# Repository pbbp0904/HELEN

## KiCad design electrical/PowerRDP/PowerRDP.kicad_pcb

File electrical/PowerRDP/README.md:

# RDP-Power
This is a PCB designed in KiCad for the UAH SHC HELEN project's Radiation Detection Payload (RDP).  This PCB is intended to receive power from 2-3 18650 battery "banks" with 2 batteries connecting to each of J1:6.  Then the voltage is stepped to appropriate levels for the power requirements of the RDP payload (+/-15V, +12V and +3.3V).  A BOM will be attached after a parts list is fully compiled.

The rendering above is a rough idea of what this payload will look like with most of its components installed.  It is only missing the +/-15 V regulator in the bottom right and the mounting screws.

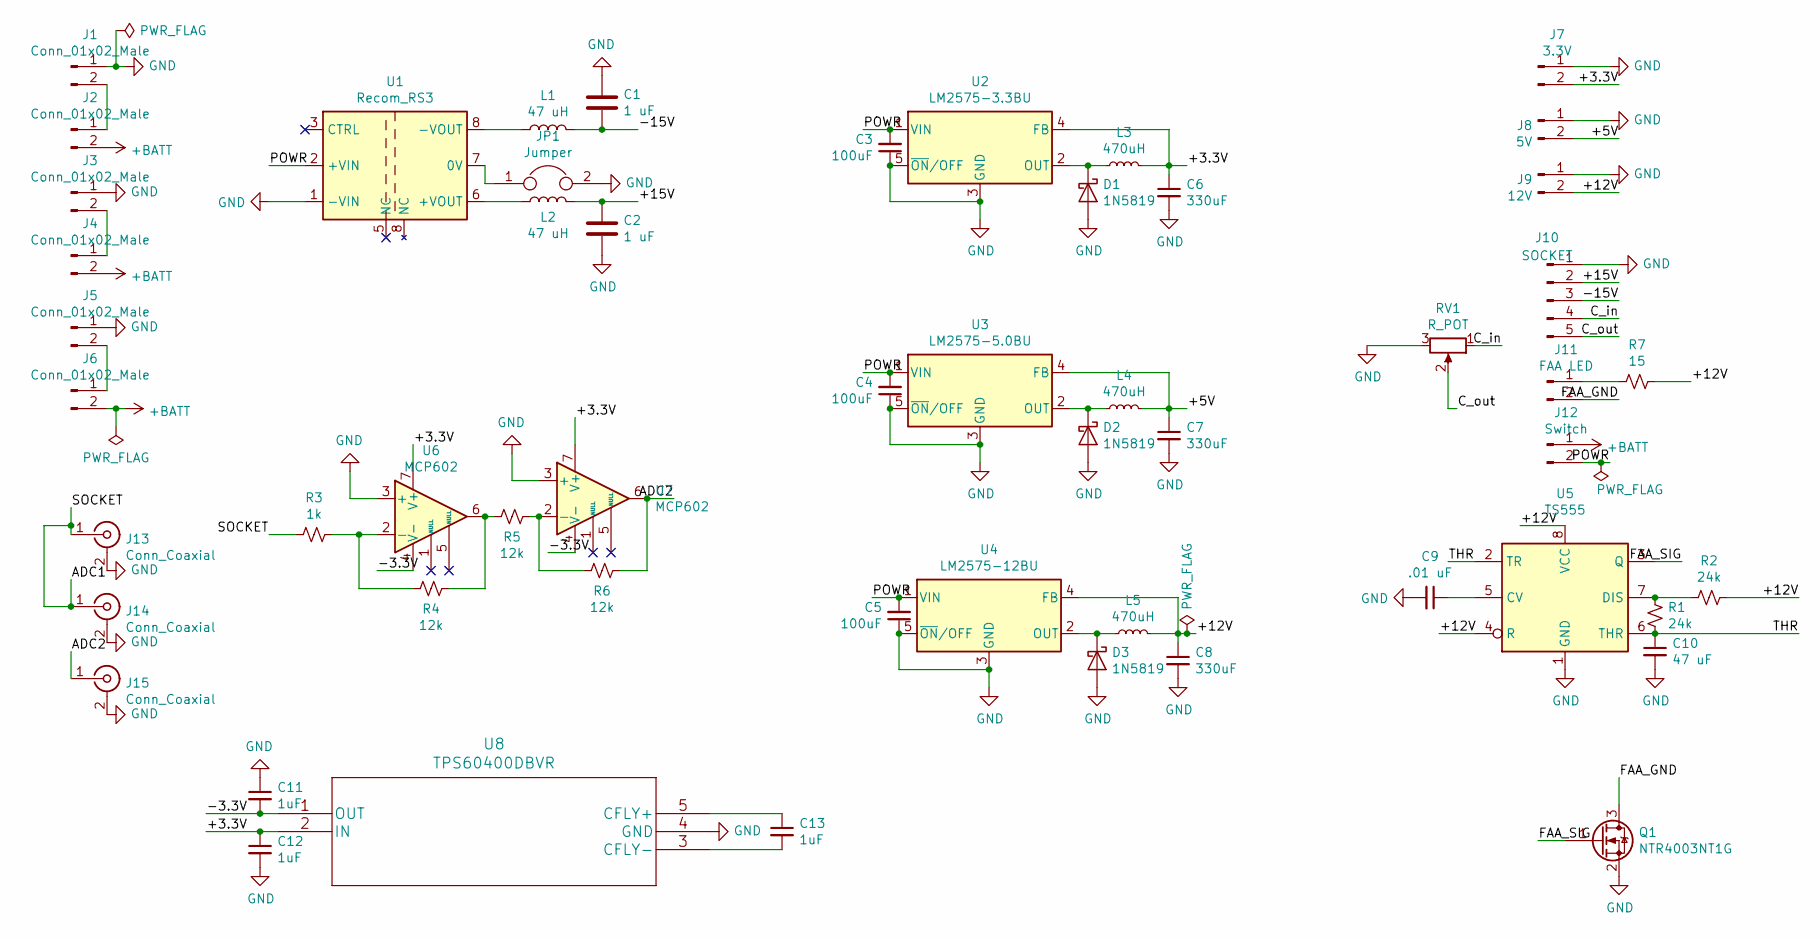
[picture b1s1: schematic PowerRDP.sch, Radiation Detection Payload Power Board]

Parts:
C1, C2: 1 uF; C_0805_2012Metric_Pad1.15x1.40mm_HandSolder
C3, C4, C5: 100uF; CP_Elec_6.3x7.7
C6, C7, C8: 330uF; CP_Elec_8x10
C9: .01 uF; C_0805_2012Metric_Pad1.15x1.40mm_HandSolder
C10: 47 uF; C_0805_2012Metric_Pad1.15x1.40mm_HandSolder
C11, C12, C13: 1uF; C_0805_2012Metric_Pad1.15x1.40mm_HandSolder
D1, D2, D3: 1N5819; D_SOD-123
J1, J2, J3, J4, J5, J6: Conn_01x02_Male; Molex_KK-254_AE-6410-02A_1x02_P2.54mm_Vertical
J7: 3.3V; Molex_KK-254_AE-6410-02A_1x02_P2.54mm_Vertical
J8: 5V; Molex_KK-254_AE-6410-02A_1x02_P2.54mm_Vertical
J9: 12V; Molex_KK-254_AE-6410-02A_1x02_P2.54mm_Vertical
J10: SOCKET; Molex_KK-254_AE-6410-05A_1x05_P2.54mm_Vertical
J11: FAA LED; Molex_KK-254_AE-6410-02A_1x02_P2.54mm_Vertical
J12: Switch; Molex_KK-254_AE-6410-02A_1x02_P2.54mm_Vertical
J13, J14, J15: Conn_Coaxial; SMA_Amphenol_132134_Vertical
JP1: Jumper; SolderJumper-2_P1.3mm_Open_Pad1.0x1.5mm
L1, L2: 47 uH; Murata 8200
L3, L4, L5: 470uH; L_Bourns_SRR1260
Q1: NTR4003NT1G; TSOT-23_HandSoldering
R1, R2: 24k; R_0805_2012Metric_Pad1.15x1.40mm_HandSolder
R3: 1k; R_Axial_DIN0204_L3.6mm_D1.6mm_P5.08mm_Horizontal
R4, R5, R6: 12k; R_0805_2012Metric_Pad1.15x1.40mm_HandSolder
R7: 15; R_0805_2012Metric_Pad1.15x1.40mm_HandSolder
RV1: R_POT; Potentiometer_Bourns_3214W_Vertical
U1: Recom_RS3
U2: LM2575-3.3BU; TO-263-5_TabPin3
U3: LM2575-5.0BU; TO-263-5_TabPin3
U4: LM2575-12BU; TO-263-5_TabPin3
U5: TS555; SOIC-8_3.9x4.9mm_P1.27mm
U6, U7: MCP602; SOIC-8_3.9x4.9mm_P1.27mm
U8: TPS60400DBVR

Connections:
+BATT: J2.2, J4.2, J6.2, J12.1
/+3.3V: C6.1, C12.1, J7.2, L3.2, U2.4 (FB), U6.7 (V+), U7.7 (V+), U8.2 (IN)
/+5V: C7.1, J8.2, L4.2, U3.4 (FB)
/+12V: C8.1, J9.2, L5.2, R2.1, R7.1, U4.4 (FB), U5.4 (R), U5.8 (VCC)
/+15V: C2.1, J10.2, L2.2
/-3.3V: C11.2, U6.4 (V-), U7.4 (V-), U8.1 (OUT)
/-15V: C1.1, J10.3, L1.2
/ADC1: J13.1 (In), J14.1 (In), R3.2
/ADC2: J15.1 (In), R6.1, U7.6
/C_in: J10.4, RV1.1
/C_out: J10.5, RV1.2
/FAA_GND: J11.2, Q1.3 (D)
/FAA_SIG: Q1.1 (G), U5.3 (Q)
/POWR: C3.2, C4.2, C5.2, J12.2, U1.2 (+VIN), U2.1 (VIN), U3.1 (VIN), U4.1 (VIN)
/THR: C10.1, R1.2, U5.2 (TR), U5.6 (THR)
GND: C1.2, C2.2, C3.1, C4.1, C5.1, C6.2, C7.2, C8.2, C9.2, C10.2, C11.1, C12.2, D1.2 (A), D2.2 (A), D3.2 (A), J1.1, J3.1, J5.1, J7.1, J8.1, J9.1, J10.1, J13.2 (Ext), J14.2 (Ext), J15.2 (Ext), JP1.2, Q1.2 (S), RV1.3, U1.1 (-VIN), U2.3 (GND), U2.5 (~ON~/OFF), U3.3 (GND), U3.5 (~ON~/OFF), U4.3 (GND), U4.5 (~ON~/OFF), U5.1 (GND), U6.3 (+), U7.3 (+), U8.4 (GND)
unnamed: C9.1, U5.5 (CV)
unnamed: C13.1, U8.5 (CFLY+)
unnamed: C13.2, U8.3 (CFLY-)
unnamed: D1.1 (K), L3.1, U2.2 (OUT)
unnamed: D2.1 (K), L4.1, U3.2 (OUT)
unnamed: D3.1 (K), L5.1, U4.2 (OUT)
unnamed: J1.2, J2.1
unnamed: J3.2, J4.1
unnamed: J5.2, J6.1
unnamed: J11.1, R7.2
unnamed: JP1.1, U1.7 (0V)
unnamed: L1.1, U1.8 (-VOUT)
unnamed: L2.1, U1.6 (+VOUT)
unnamed: R1.1, R2.2, U5.7 (DIS)
unnamed: R3.1, R4.2, U6.2 (-)
unnamed: R4.1, R5.2, U6.6
unnamed: R5.1, R6.2, U7.2 (-)

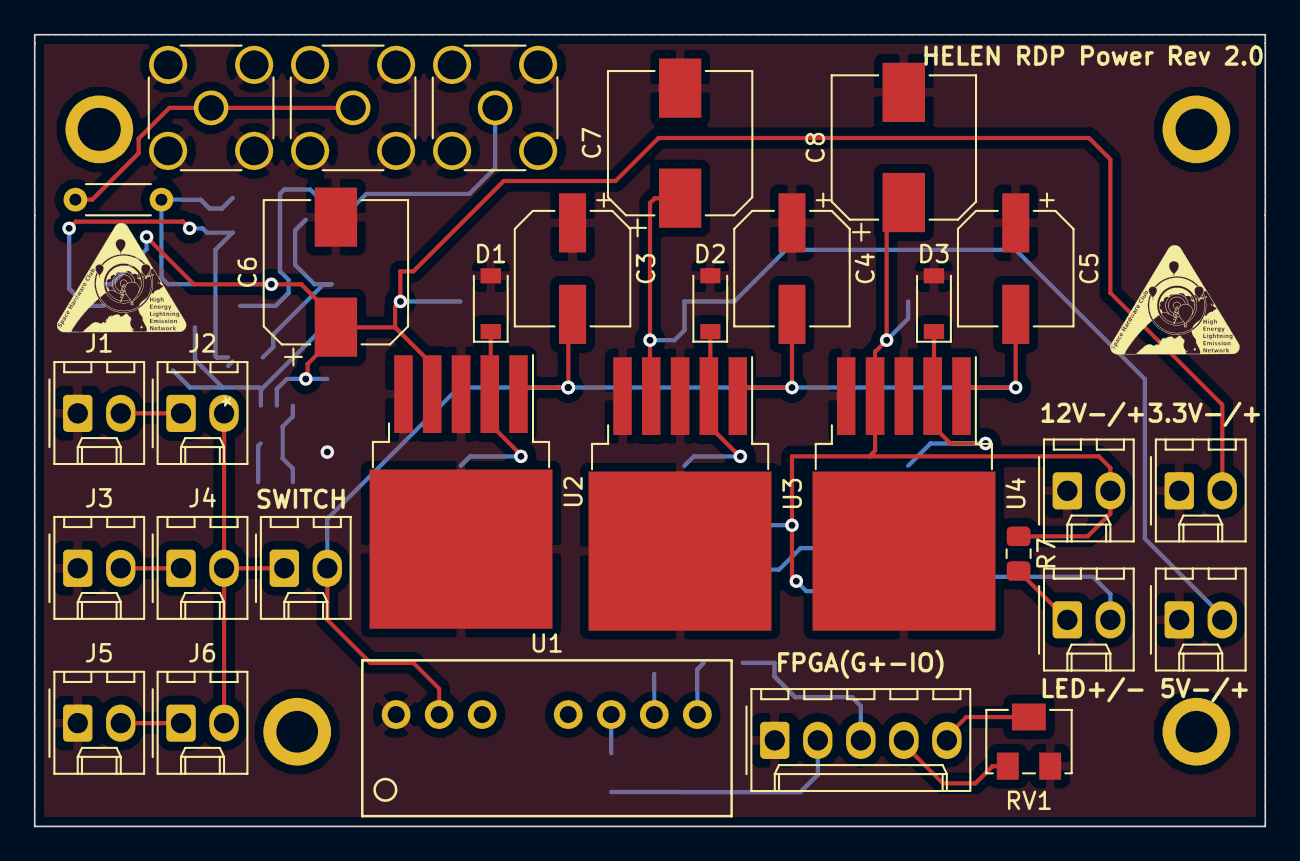
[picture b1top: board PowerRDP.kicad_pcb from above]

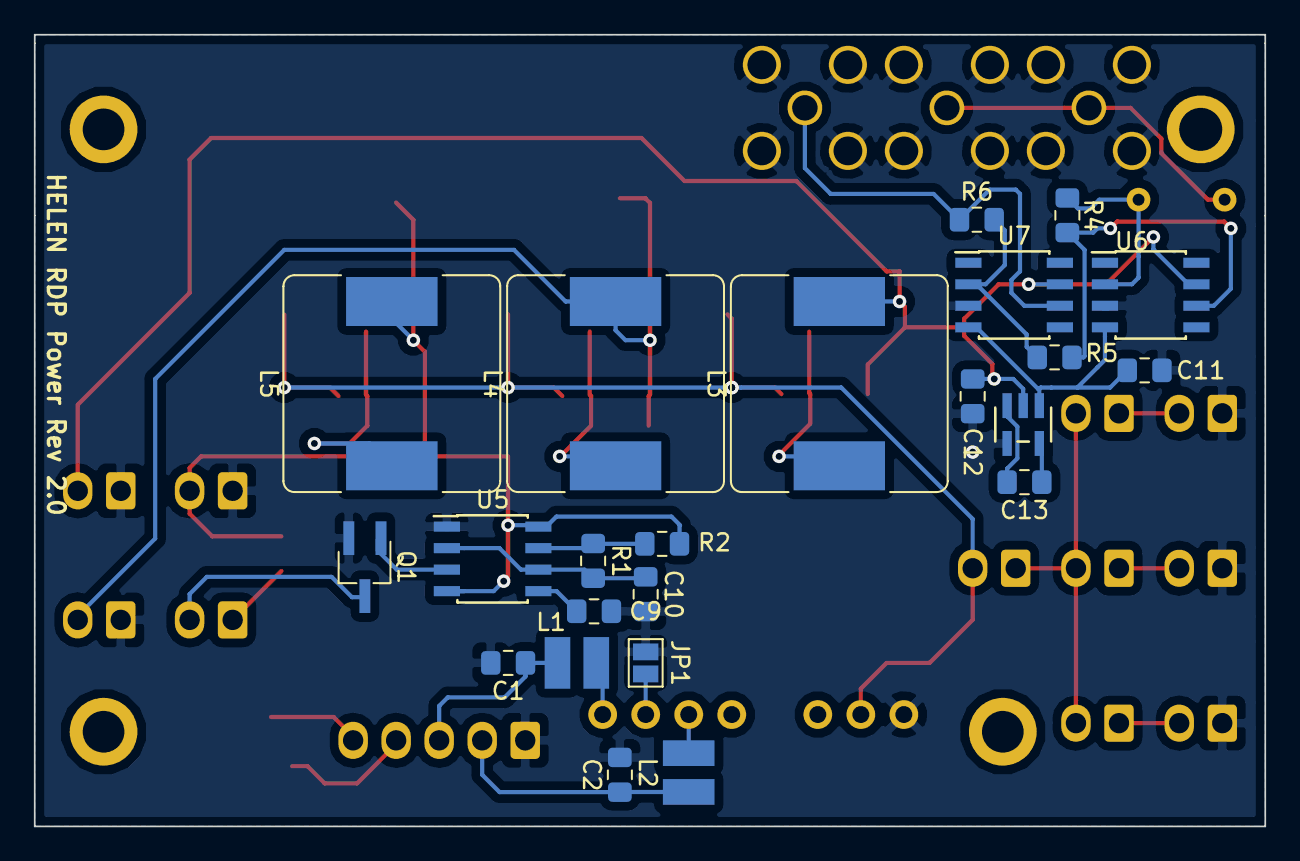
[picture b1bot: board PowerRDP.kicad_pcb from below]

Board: 2 copper layers, 72.6 x 46.7 mm, 54 parts (23 on the bottom side), 33 nets.

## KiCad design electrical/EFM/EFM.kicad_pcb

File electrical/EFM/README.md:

# Electric Field Meter
This is a PCB designed in KiCad for the UAH SHC HELEN project's Electric Field Meter.  This PCB is intended to receive a current on the two-input molex connector that will vary as two metal spheres spin around several axes in a thunderstorm.  The current is converted to a readable voltage and then shifted up utilizing a weighted summer and the -2.8V line used to power the opamps.  It is shifted such that it approximately maximizes the range that the MCU's ADC can read while powered with 2.8V, from ~0-1.2V.

The rendering above is a rough idea of what this payload will look like with some of its components installed.

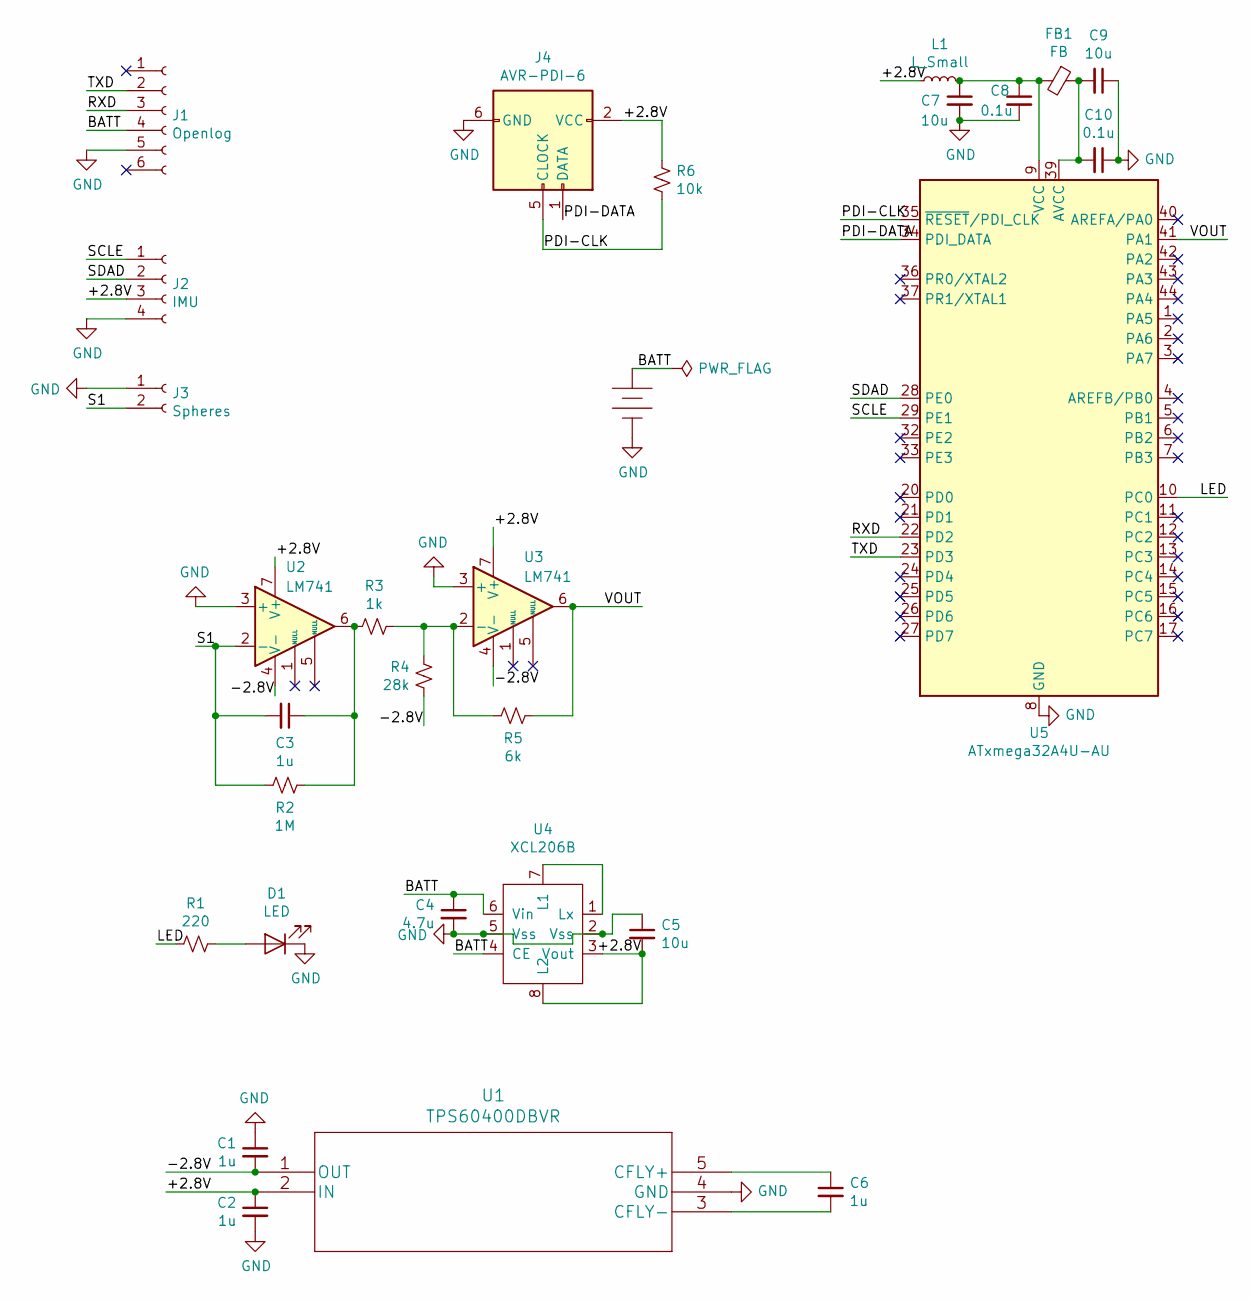
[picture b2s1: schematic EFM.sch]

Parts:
C1, C2, C3, C6: 1u; C_0805_2012Metric_Pad1.15x1.40mm_HandSolder
C4: 4.7u; C_0805_2012Metric_Pad1.15x1.40mm_HandSolder
C5, C7, C9: 10u; C_0805_2012Metric_Pad1.15x1.40mm_HandSolder
C8, C10: 0.1u; C_0805_2012Metric_Pad1.15x1.40mm_HandSolder
D1: LED; LED_0805_2012Metric
FB1: FB; L_0805_2012Metric_Pad1.15x1.40mm_HandSolder
J1: Openlog; Molex_KK-254_AE-6410-06A_1x06_P2.54mm_Vertical
J2: IMU; Molex_KK-254_AE-6410-04A_1x04_P2.54mm_Vertical
J3: Spheres; Molex_KK-254_AE-6410-02A_1x02_P2.54mm_Vertical
J4: AVR-PDI-6; PinHeader_2x03_P2.54mm_Vertical
L1: L_Small; L_0805_2012Metric_Pad1.15x1.40mm_HandSolder
M1: SHC_123_BATTERY_HOLDERCR-123-A; SHC_CR-123-A_HOLDER
R1: 220; R_0805_2012Metric_Pad1.15x1.40mm_HandSolder
R2: 1M; R_0805_2012Metric_Pad1.15x1.40mm_HandSolder
R3: 1k; R_0805_2012Metric_Pad1.15x1.40mm_HandSolder
R4: 28k; R_0805_2012Metric_Pad1.15x1.40mm_HandSolder
R5: 6k; R_0805_2012Metric_Pad1.15x1.40mm_HandSolder
R6: 10k; R_0805_2012Metric_Pad1.15x1.40mm_HandSolder
U1: TPS60400DBVR
U2, U3: LM741; SOIC-8_3.9x4.9mm_P1.27mm
U4: XCL206B; 6-TDFN
U5: ATxmega32A4U-AU; TQFP-44_10x10mm_P0.8mm

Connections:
/+2.8V: C2.1, C5.2, J2.3, J4.2 (VCC), L1.1, R6.1, U1.2 (IN), U2.7 (V+), U3.7 (V+), U4.3 (Vout), U4.8 (L2)
/-2.8V: C1.2, R4.2, U1.1 (OUT), U2.4 (V-), U3.4 (V-)
/BATT: C4.1, J1.4, M1.+, U4.4 (CE), U4.6 (Vin)
/LED: R1.2, U5.10 (PC0)
/PDI-CLK: J4.5 (CLOCK), R6.2, U5.35 (~RESET~/PDI_CLK)
/PDI-DATA: J4.1 (DATA), U5.34 (PDI_DATA)
/RXD: J1.3, U5.22 (PD2)
/S1: C3.2, J3.2, R2.2, U2.2 (-)
/SCLE: J2.1, U5.29 (PE1)
/SDAD: J2.2, U5.28 (PE0)
/TXD: J1.2, U5.23 (PD3)
/VOUT: R5.1, U3.6, U5.41 (PA1)
GND: C1.1, C2.2, C4.2, C5.1, C7.2, C8.2, C9.1, C10.1, D1.1 (K), J1.5, J2.4, J3.1, J4.6 (GND), M1.-, U1.4 (GND), U2.3 (+), U3.3 (+), U4.2 (Vss), U4.5 (Vss), U5.8 (GND), U5.18 (GND), U5.30 (GND), U5.38 (GND)
unnamed: C3.1, R2.1, R3.2, U2.6
unnamed: C6.1, U1.5 (CFLY+)
unnamed: C6.2, U1.3 (CFLY-)
unnamed: C7.1, C8.1, FB1.2, L1.2, U5.9 (VCC), U5.19 (VCC), U5.31 (VCC)
unnamed: C9.2, C10.2, FB1.1, U5.39 (AVCC)
unnamed: D1.2 (A), R1.1
unnamed: R3.1, R4.1, R5.2, U3.2 (-)
unnamed: U4.1 (Lx), U4.7 (L1)

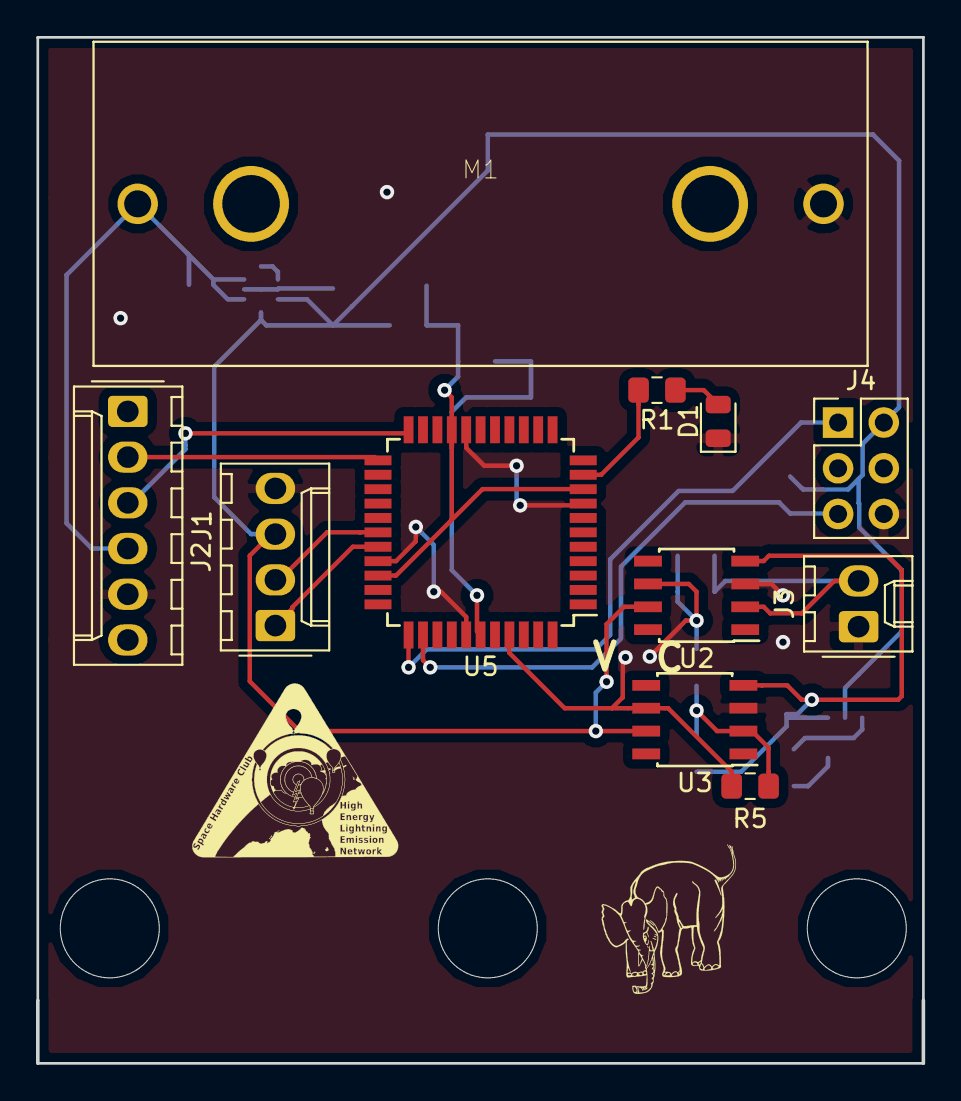
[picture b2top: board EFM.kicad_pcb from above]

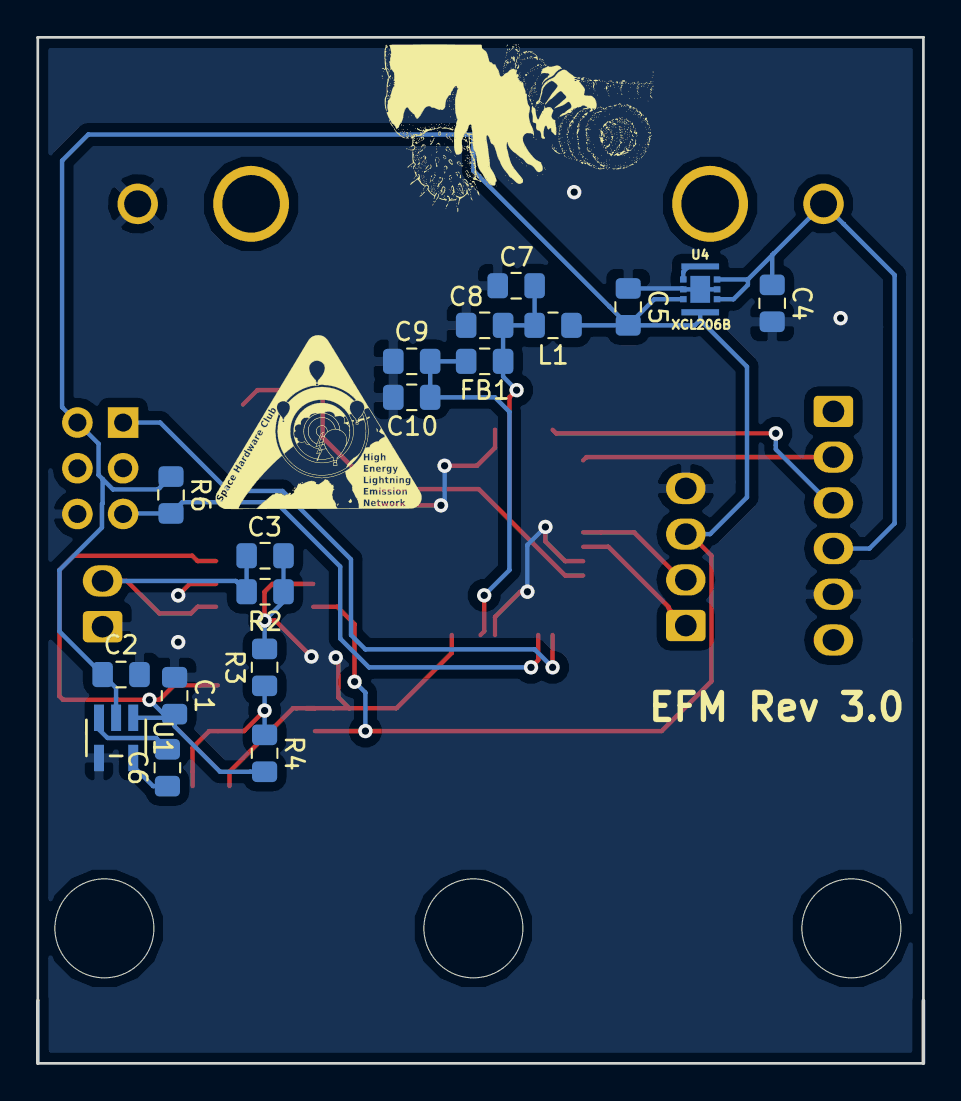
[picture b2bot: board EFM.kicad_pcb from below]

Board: 2 copper layers, 49.2 x 57.0 mm, 29 parts (18 on the bottom side), 21 nets.

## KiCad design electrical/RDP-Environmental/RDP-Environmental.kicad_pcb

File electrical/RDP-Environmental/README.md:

# RDP-Environmental
This is a PCB designed in KiCad for the UAH SHC HELEN project's Radiation Detection Payload (RDP). This board is intended to gather environmental inupt including temperature, pressure and GPS.  This information is processed and saved and potentially shared with an external FPGA.

The rendering above is a rough idea of what this payload will look like with some of its components installed.

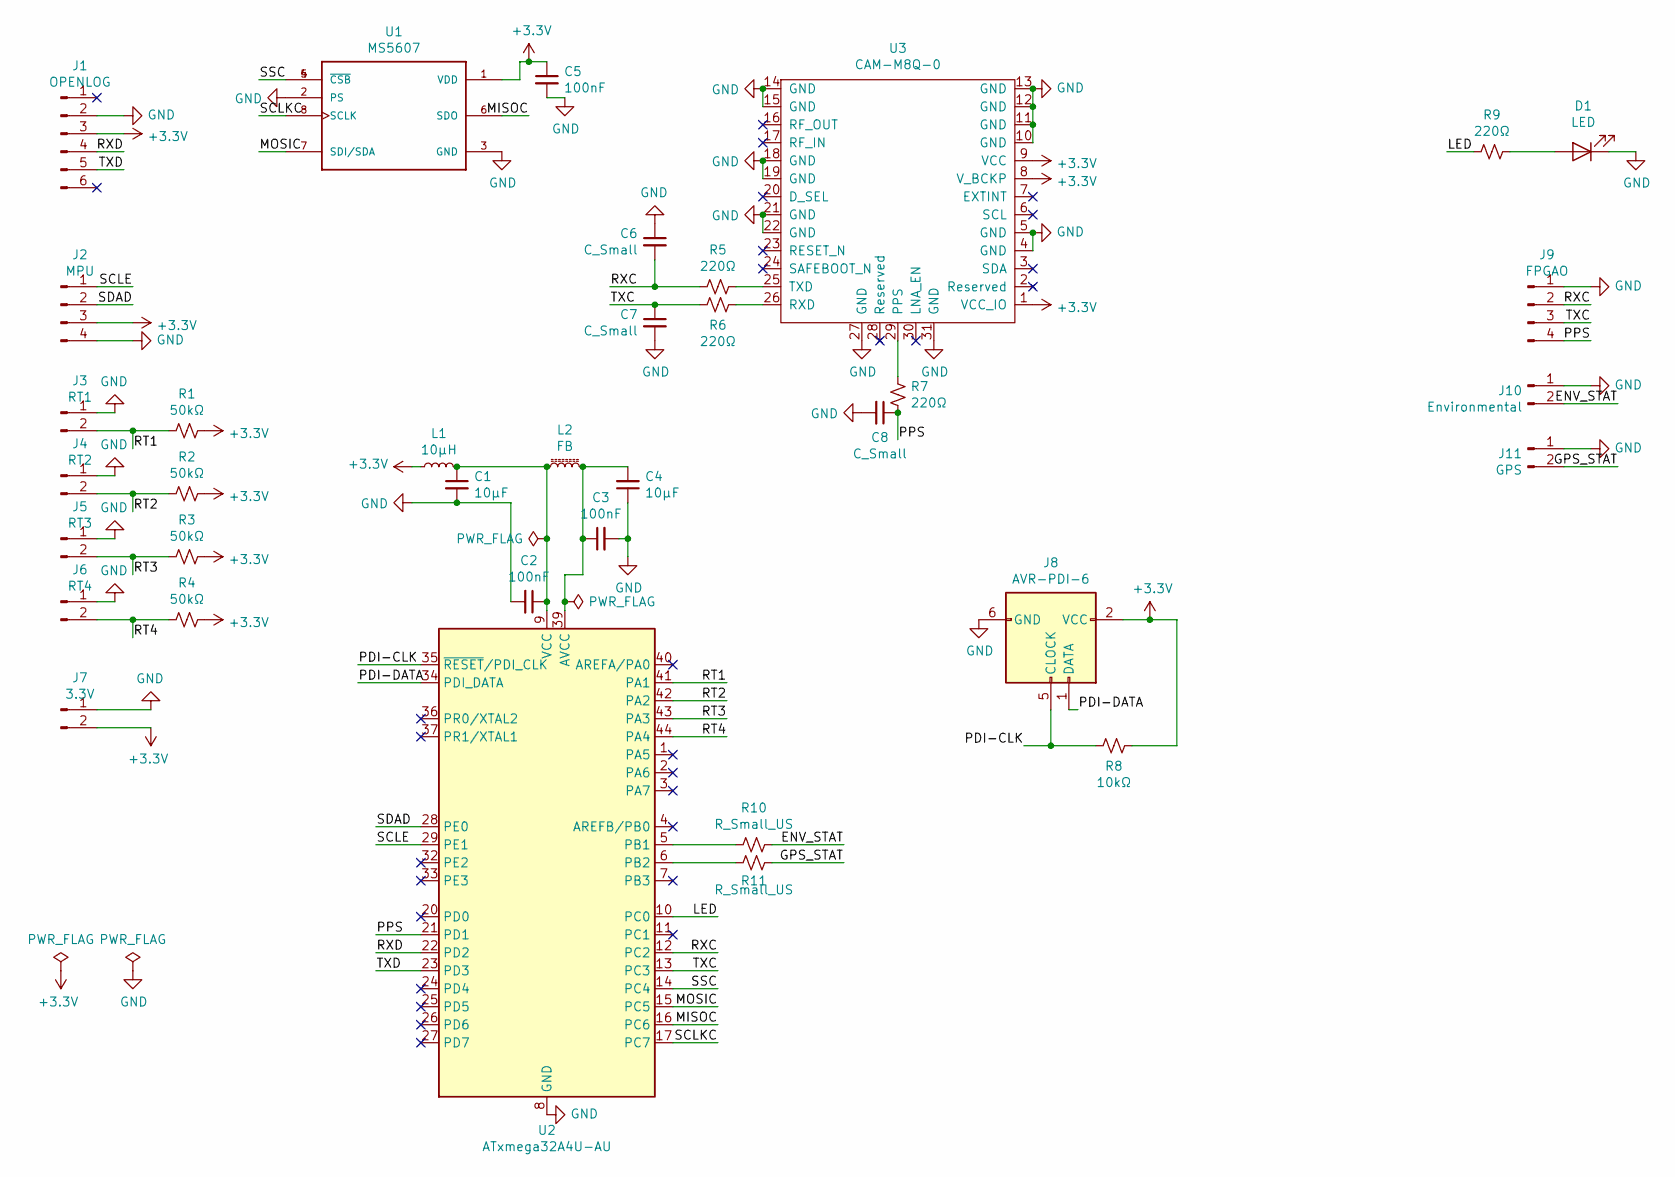
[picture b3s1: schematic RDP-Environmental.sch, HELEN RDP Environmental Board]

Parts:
C1, C4: 10μF; C_0805_2012Metric_Pad1.15x1.40mm_HandSolder
C2, C3, C5: 100nF; C_0805_2012Metric_Pad1.15x1.40mm_HandSolder
C6, C7, C8: C_Small; C_0805_2012Metric_Pad1.15x1.40mm_HandSolder
D1: LED; LED_0603_1608Metric
J1: OPENLOG; PinHeader_1x06_P2.54mm_Vertical
J2: MPU; PinHeader_1x04_P2.54mm_Vertical
J3: RT1; Molex_KK-254_AE-6410-02A_1x02_P2.54mm_Vertical
J4: RT2; Molex_KK-254_AE-6410-02A_1x02_P2.54mm_Vertical
J5: RT3; Molex_KK-254_AE-6410-02A_1x02_P2.54mm_Vertical
J6: RT4; Molex_KK-254_AE-6410-02A_1x02_P2.54mm_Vertical
J7: 3.3V; Molex_KK-254_AE-6410-02A_1x02_P2.54mm_Vertical
J8: AVR-PDI-6; PinHeader_2x03_P2.54mm_Vertical
J9: FPGAO; Molex_KK-254_AE-6410-04A_1x04_P2.54mm_Vertical
J10: Environmental; Molex_KK-254_AE-6410-02A_1x02_P2.54mm_Vertical
J11: GPS; Molex_KK-254_AE-6410-02A_1x02_P2.54mm_Vertical
L1: 10μH; L_0805_2012Metric_Pad1.15x1.40mm_HandSolder
L2: FB; L_0805_2012Metric_Pad1.15x1.40mm_HandSolder
R1, R2, R3, R4: 50kΩ; R_0805_2012Metric_Pad1.15x1.40mm_HandSolder
R5, R6, R7, R9: 220Ω; R_0805_2012Metric_Pad1.15x1.40mm_HandSolder
R8: 10kΩ; R_0805_2012Metric_Pad1.15x1.40mm_HandSolder
R10, R11: R_Small_US; R_0805_2012Metric_Pad1.15x1.40mm_HandSolder
U1: MS5607; SON125P300X500X100-8N
U2: ATxmega32A4U-AU; TQFP-44_10x10mm_P0.8mm
U3: CAM-M8Q-0; CAM-M8

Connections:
+3V3: C5.1, J1.3, J2.3, J7.2, J8.2 (VCC), L1.1, R1.1, R2.1, R3.1, R4.1, R8.2, U1.1 (VDD), U3.1 (VCC_IO), U3.8 (V_BCKP), U3.9 (VCC)
/ENV_STAT: J10.2, R10.1
/GPS_STAT: J11.2, R11.2
/LED: R9.2, U2.10 (PC0)
/MISOC: U1.6 (SDO), U2.16 (PC6)
/MOSIC: U1.7 (SDI/SDA), U2.15 (PC5)
/PDI-CLK: J8.5 (CLOCK), R8.1, U2.35 (~RESET~/PDI_CLK)
/PDI-DATA: J8.1 (DATA), U2.34 (PDI_DATA)
/PPS: C8.1, J9.4, R7.1, U2.21 (PD1)
/RT1: J3.2, R1.2, U2.41 (PA1)
/RT2: J4.2, R2.2, U2.42 (PA2)
/RT3: J5.2, R3.2, U2.43 (PA3)
/RT4: J6.2, R4.2, U2.44 (PA4)
/RXC: C6.2, J9.2, R5.2, U2.12 (PC2)
/RXD: J1.4, U2.22 (PD2)
/SCLE: J2.1, U2.29 (PE1)
/SCLKC: U1.8 (SCLK), U2.17 (PC7)
/SDAD: J2.2, U2.28 (PE0)
/SSC: U1.4 (~CSB~), U1.5 (~CSB~), U2.14 (PC4)
/TXC: C7.1, J9.3, R6.2, U2.13 (PC3)
/TXD: J1.5, U2.23 (PD3)
GND: C1.2, C2.2, C3.2, C4.1, C5.2, C6.1, C7.2, C8.2, D1.1 (K), J1.2, J2.4, J3.1, J4.1, J5.1, J6.1, J7.1, J8.6 (GND), J9.1, J10.1, J11.1, U1.2 (PS), U1.3 (GND), U2.8 (GND), U2.18 (GND), U2.30 (GND), U2.38 (GND), U3.4 (GND), U3.5 (GND), U3.10 (GND), U3.11 (GND), U3.12 (GND), U3.13 (GND), U3.14 (GND), U3.15 (GND), U3.18 (GND), U3.19 (GND), U3.21 (GND), U3.22 (GND), U3.27 (GND), U3.31 (GND); also elsewhere on the board
unnamed 22: C1.1, C2.1, L1.2, L2.1, U2.9 (VCC), U2.19 (VCC), U2.31 (VCC); also elsewhere on the board
unnamed: C3.1, C4.2, L2.2, U2.39 (AVCC)
unnamed: D1.2 (A), R9.1
unnamed: R5.1, U3.25 (TXD)
unnamed: R6.1, U3.26 (RXD)
unnamed: R7.2, U3.29 (PPS)
unnamed: R10.2, U2.5 (PB1)
unnamed: R11.1, U2.6 (PB2)

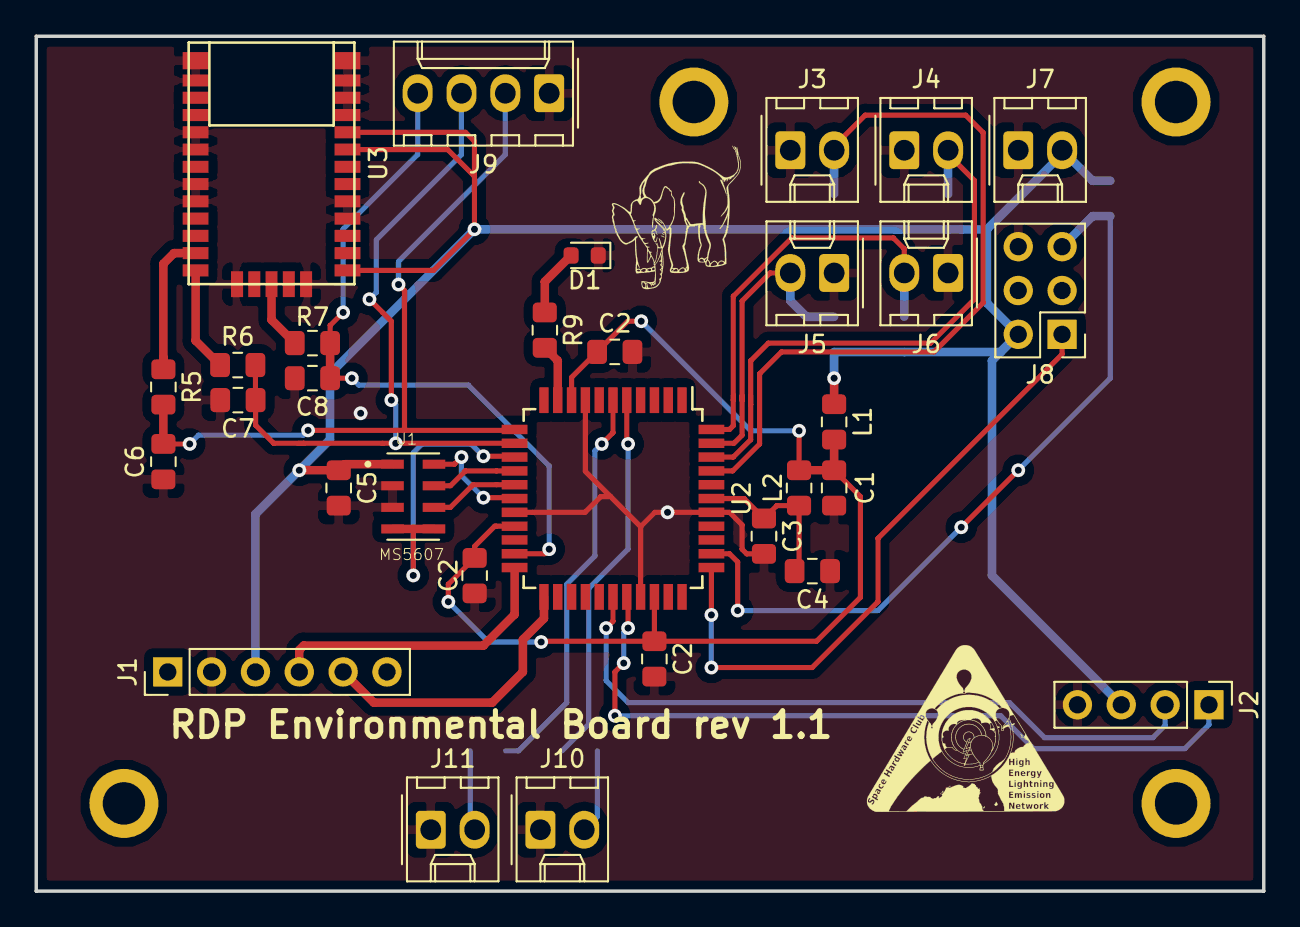
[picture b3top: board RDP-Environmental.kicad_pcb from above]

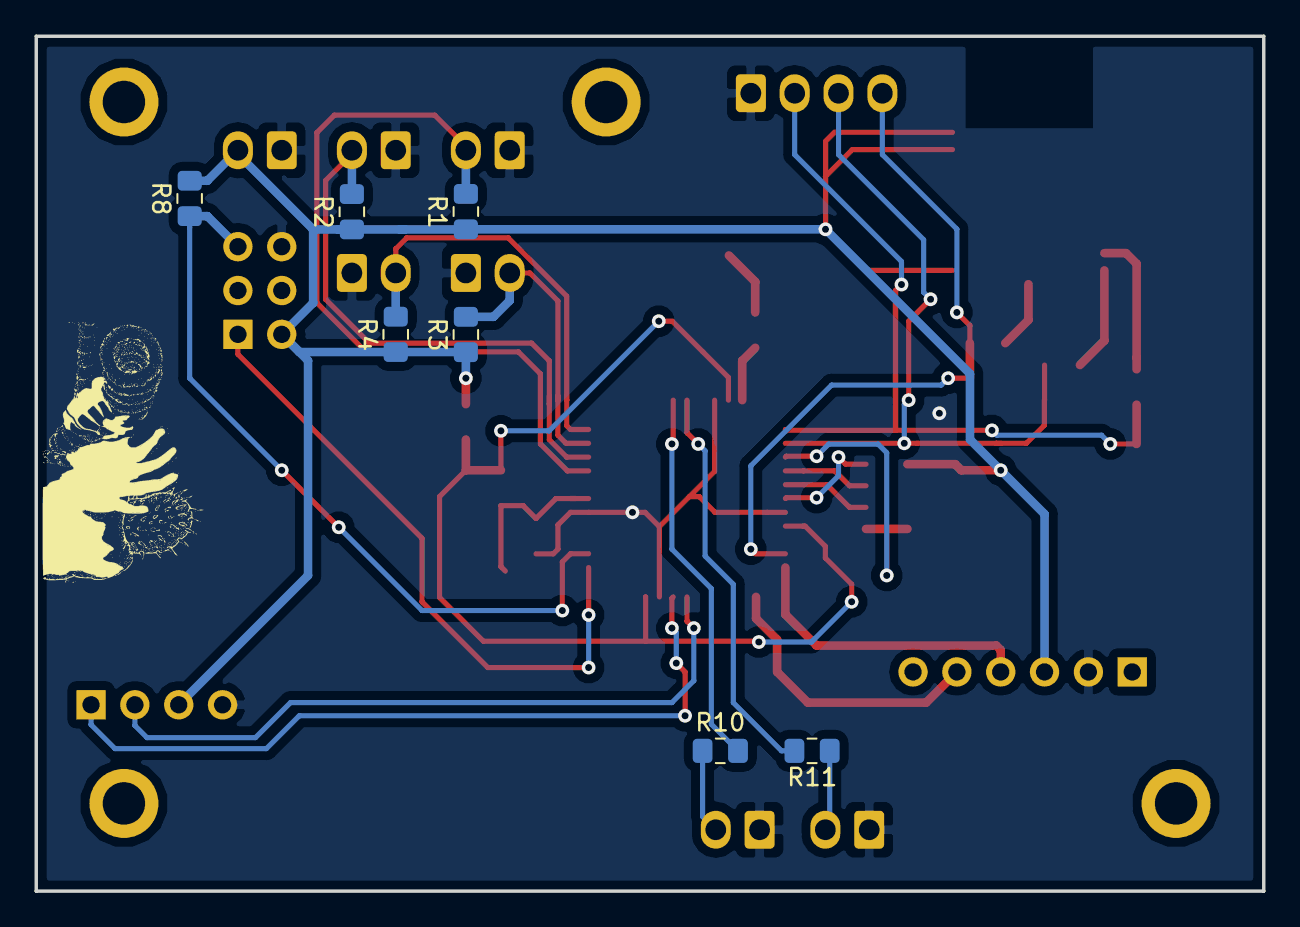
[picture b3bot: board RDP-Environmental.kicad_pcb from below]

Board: 2 copper layers, 71.1 x 49.5 mm, 38 parts (7 on the bottom side), 30 nets.

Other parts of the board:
C2#2, C2#3: 100nF; C_0805_2012Metric_Pad1.15x1.40mm_HandSolder

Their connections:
GND: C2#2.2, C2#3.2; also elsewhere on the board
unnamed 22: C2#2.1, C2#3.1; also elsewhere on the board

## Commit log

2019-04-19 add software things
2019-04-19 Add electrical filed
2019-04-19 dave
    gredg
2019-04-19 Added Sim Files
2019-04-20 test
2019-04-20 remove test
2019-08-08 add all work from summer
2019-08-08 add hps scripts
2019-08-08 change peak to tail distance to 22
2019-08-09 change distance from peak to tail to 25
2019-08-09 change peak to tail difference to 100 nanoseconds
2019-08-09 modify peak to tail
2019-08-09 change peak to tail to 170 ns
2019-08-20 chris additional work
2019-08-23 cleanup and formatting
2019-08-23 preliminary verilog algorithm for saving full pulse
2019-08-29 fix things
2019-08-29 change to channel a and complete algorithm
2019-08-29 big fix time, finish full data collection algo
2019-09-03 add 32 data transfer pio ports
2019-09-04 recover hps scripts from previous commit
2019-09-04 generate tcl script and extract base addresses from it
2019-09-05 add base addresses to fpga.cpp
2020-01-09 make updates to full pulse saving, added pps counter
2020-01-09 add qtcreator stuff, change fpga and writer a bit
2020-01-09 added full pulse HPS work
2020-01-10 fix ddc dcc error
2021-11-30 added EFM Sphere Board

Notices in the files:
parts and their libraries:
Copyright 2016 Accelerated Designs. All rights reserved.
